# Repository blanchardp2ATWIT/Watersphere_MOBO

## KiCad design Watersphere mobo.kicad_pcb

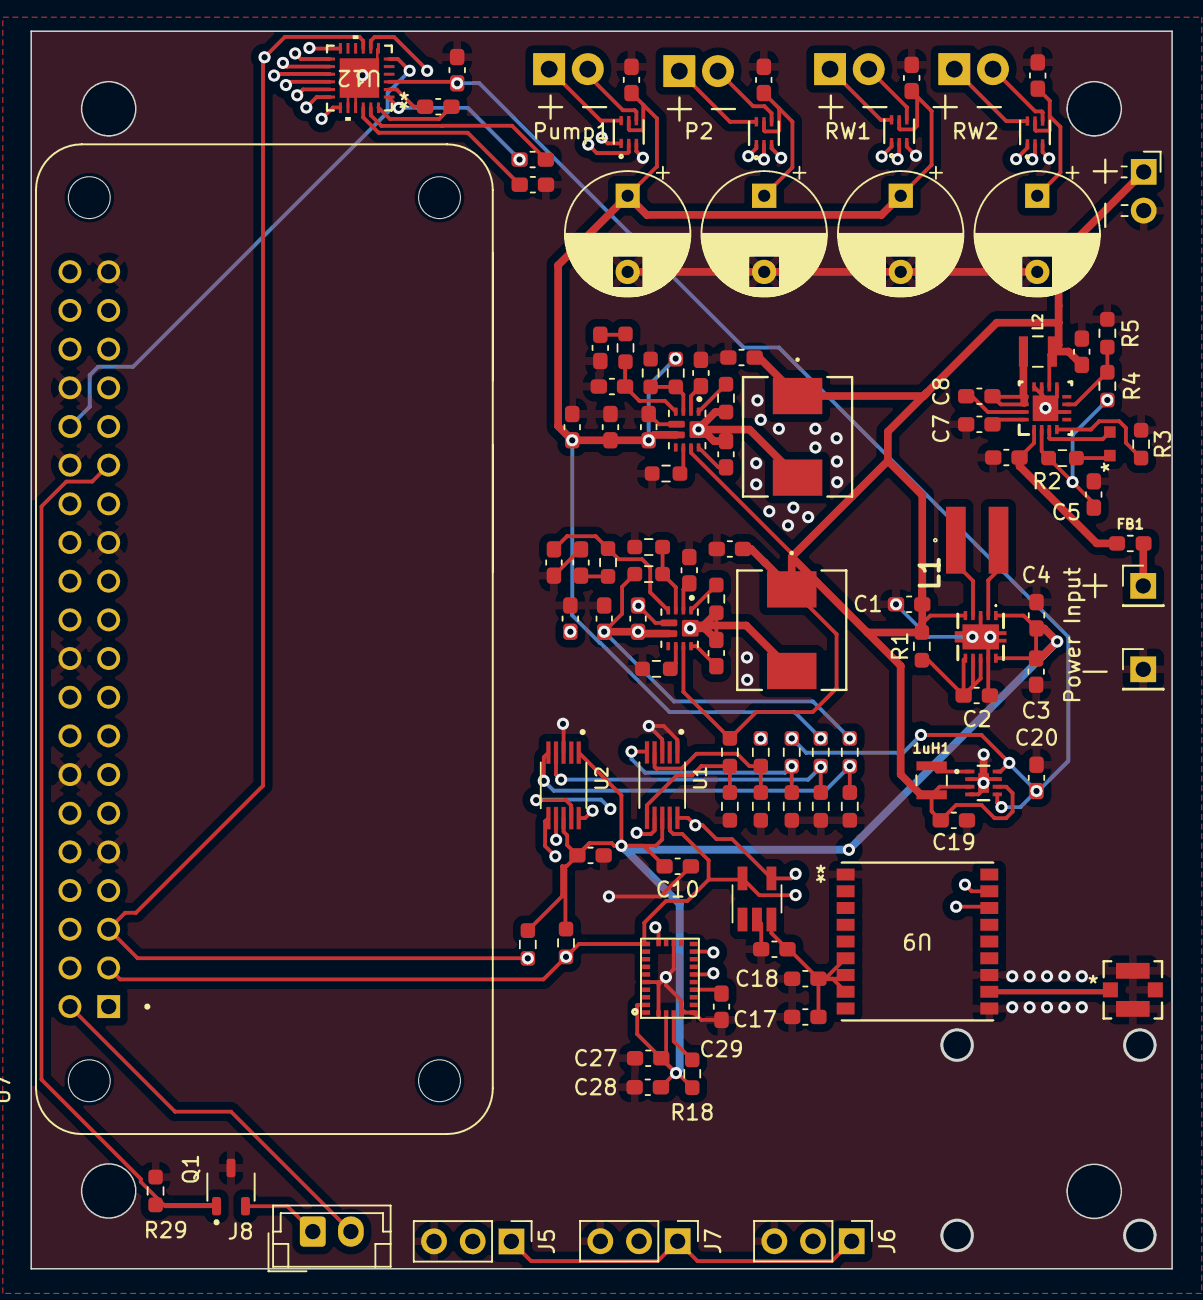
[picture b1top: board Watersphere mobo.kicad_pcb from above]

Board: 4 copper layers, 74.9 x 81.3 mm, 112 parts (0 on the bottom side), 73 nets.

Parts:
1uH1: VLS252012HBX-1R0M-1; IND_VLS252012HBX-1R0M-1
100uF1, 100uF2, 100uF3, 100uF4: C_Polarized; CP_Radial_D8.0mm_P5.00mm
C1, C3, C4, C7, C9, C17: 10 uF; C_0603_1608Metric_Pad1.08x0.95mm_HandSolder
C2: 100 nF; C_0603_1608Metric_Pad1.08x0.95mm_HandSolder
C5, C6: 2.2 uF; C_0603_1608Metric_Pad1.08x0.95mm_HandSolder
C8: 47 nF; C_0603_1608Metric_Pad1.08x0.95mm_HandSolder
C10, C11, C16, C25, C26: 1 uF; C_0603_1608Metric_Pad1.08x0.95mm_HandSolder
C12, C13, C21, C22, C27, C28, C29: .1 uF; C_0603_1608Metric_Pad1.08x0.95mm_HandSolder
C14, C30, C31, C32, C38, C39, C41, C42: 22uF; C_0603_1608Metric_Pad1.08x0.95mm_HandSolder
C15, C18, C40: 100nF; C_0603_1608Metric_Pad1.08x0.95mm_HandSolder
C19: 4.7 uF; C_0603_1608Metric_Pad1.08x0.95mm_HandSolder
C20: 22 uF; C_0603_1608Metric_Pad1.08x0.95mm_HandSolder
C23: .47 uf; C_0603_1608Metric_Pad1.08x0.95mm_HandSolder
C24: .47 uF; C_0603_1608Metric_Pad1.08x0.95mm_HandSolder
C33, C43: 2.2uF; C_0603_1608Metric_Pad1.08x0.95mm_HandSolder
C34, C37: 4.7nf; C_0603_1608Metric_Pad1.08x0.95mm_HandSolder
C35, C36: optional; C_0603_1608Metric_Pad1.08x0.95mm_HandSolder
D1: LTST-C190KRKT; LED_150060GS75000_WRE-M
IC1: BQ25303JRTER; RTE0016C_NV
J2, J3: Conn_01x01_Pin; PinHeader_1x01_P2.54mm_Vertical
J4: 691213710002; PinSocket_1x02_P2.54mm_Horizontal
J5, J6, J7: Pressure Sensor I/O; PinHeader_1x03_P2.54mm_Vertical
J8: JST_02; JST_EH_B2B-EH-A_1x02_P2.50mm_Vertical
L1: 2.2 uH; VLS4012
L2: 1 uH; IND_VLS252012HBX-1R0M-1
L3, L4: 1.8uH; IND_7030-WE-LHMI_WRE-L
MC1: SOT-23-5_HandSoldering
MI0603M121R-1: 100 ohm; L_0603_1608Metric_Pad1.05x0.95mm_HandSolder
Pump1, Pump2: Screw_Terminal_01x02; TerminalBlock_TE_282834-2_1x02_P2.54mm_Horizontal
Pump1Controller1, Pump2Controller1: DRV8212DRLR; SOT6_DRV8212_TEX-L
Q1: AO3400A; SOT95P280X125-3N
R1: 100; R_0603_1608Metric_Pad0.98x0.95mm_HandSolder
R2: 1k; R_0603_1608Metric_Pad0.98x0.95mm_HandSolder
R3: 23.2k; R_0603_1608Metric_Pad0.98x0.95mm_HandSolder
R4, R5, R6, R7, R8, R9, R10, R11, R12, R13, R14, R15, R18, R29: 10k; R_0603_1608Metric_Pad0.98x0.95mm_HandSolder
R16, R17: 3.3k; R_0603_1608Metric_Pad0.98x0.95mm_HandSolder
R19, R28: 301k; R_0603_1608Metric_Pad0.98x0.95mm_HandSolder
R20, R25: 681k; R_0603_1608Metric_Pad0.98x0.95mm_HandSolder
R21, R27: 107k; R_0603_1608Metric_Pad0.98x0.95mm_HandSolder
R22, R26: 127k; R_0603_1608Metric_Pad0.98x0.95mm_HandSolder
R23, R24: 17.4k; R_0603_1608Metric_Pad0.98x0.95mm_HandSolder
ReactionWheel1, ReactionWheel2: Screw_Terminal_01x02; TerminalBlock_TE_282834-2_1x02_P2.54mm_Horizontal
ReactionWheel1Controller1, ReactionWheel2Controller1: DRV8212DRLR; SOT6_DRV8212_TEX-L
U1, U2: ADS1115IDGSR; SOP50P490X110-10N
U3: TPS63001DRCR; TPS63002DRCT
U4: BNO055; LGA28R50P4X10_380X520X100
U5, U6: TPS61089RNRR; IC_TPS61089RNRR
U7: ADA3708; MODULE_ADA3708
U8: MIC2876-5.0YMT-TR; UDFN8_2X2_MCH-L
U9: TESEO-LIV3R; ARRAY_LIV3R_STM
U10: 734120114; 73412-0114_MOL
U12: LP55231SQE_NOPB; RTW24_TEX

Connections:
9v(1): 100uF1.1, 100uF3.1, C12.1, C21.1, C30.1, C31.1, C32.1, Pump1Controller1.5 (VM), R12.1, R20.2, ReactionWheel1Controller1.5 (VM), U5.6 (VOUT)
9v(1)_meas: R12.2, R13.1, U2.4 (AIN0)
9v(2): 100uF2.1, 100uF4.1, C13.1, C22.1, C39.1, C41.1, C42.1, Pump2Controller1.5 (VM), R14.1, R25.2, ReactionWheel2Controller1.5 (VM), U6.6 (VOUT)
9v(2)_meas: R14.2, R15.1, U2.5 (AIN1)
+3.3V: C3.1, C4.1, C10.1, C11.1, C16.2, C17.1, C18.1, C27.1, C28.1, MC1.3 (VDD), R8.1, R16.1, R17.1, R18.1, U1.8 (VDD), U2.1 (ADDR), U2.8 (VDD), U3.1 (VOUT), U3.10 (FB), U4.3 (VDD), U4.28 (VDDIO), U9.6 (VBATT), U9.7 (VCC_IO), U9.8 (VCC)
+3.3V_meas: R8.2, R9.1, U1.4 (AIN0)
+5V_meas: R10.2, R11.1, U1.5 (AIN1)
+5v: C20.1, C25.1, J5.1, J6.1, J7.1, J8.2, R10.1, U7.2 (5V_1), U8.5 (OUTS), U8.8 (OUT), U12.3 (VDD)
BAT+: 1uH1.1, C1.1, C9.1, C14.1, C19.2, C38.1, IC1.10 (BAT), J4.1, L2.2, L3.1, L4.1, R1.2, R6.1, U3.5 (VIN), U5.9 (VIN), U6.9 (VIN), U8.3 (IN), U8.6 (EN)
BAT+_meas: R6.2, R7.1, U1.6 (AIN2)
BNO_BOOTN: U4.11 (NRESET), U7.15 (GPIO22_GEN3)
BNO_Data_Ready: U4.14 (INT), U7.13 (GPIO27_GEN2)
GND: 100uF1.2, 100uF2.2, 100uF3.2, 100uF4.2, C1.2, C2.2, C3.2, C4.2, C5.2, C6.2, C7.2, C9.2, C10.2, C11.2, C12.2, C13.2, C14.2, C16.1, C17.2, C18.2, C19.1, C20.2, C21.2, C22.2, C25.2, C26.2, C27.2, C28.2, C29.2, C30.2, C31.2, C32.2, C33.2, C34.1, C35.1, C36.1, C37.1, C38.2, C39.2, C41.2, C42.2, C43.2, IC1.6 (~EN), IC1.9 (VSET), IC1.11 (GND_1), IC1.12 (GND_2), IC1.17 (EP), J3.1, J4.2, J5.3, J6.3, J7.3, MC1.2 (GND), Pump1Controller1.3 (GND), Pump2Controller1.3 (GND), Q1.3, R3.1, R5.1, R7.2, R9.2, R11.2, R13.2, R15.2, R21.2, R22.1, R26.1, R27.2, R29.2, ReactionWheel1Controller1.3 (GND), ReactionWheel2Controller1.3 (GND), U1.1 (ADDR), U1.3 (GND), U2.3 (GND), U3.3 (PGND), U3.9 (GND), U3.11 (PAD), U4.2 (GND), U4.5 (PS1), U4.6 (PS0), U4.17 (COM3), U4.25 (GNDIO), U5.5 (GND), U6.5 (GND), U7.9 (GND_1), U7.14 (GND_4), U7.20 (GND_5), U7.25 (GND_2), U7.30 (GND_6), U7.34 (GND_7), U7.39 (GND_3), U8.2 (PGND), U8.4 (AGND), U8.7 (/PG), U8.9 (AGND), U9.1 (GND), U9.10 (GND_RF), U9.12 (GND_RF), U10.2 (GROUND), U10.3 (GROUND), U10.4 (GROUND), U12.4 (GND), U12.5 (EN), U12.7 (INT), U12.10 (TRIG), U12.20 (ASELO), U12.21 (ASEL1)
I2C_Bus1_SCL: MC1.4 (SCL), R17.2, U1.10 (SCL), U2.10 (SCL), U4.19 (COM1), U7.5 (GPIO3_SCL), U9.17 (SCL), U12.9 (SCL)
I2C_Bus1_SDA: MC1.5 (SDA), R16.2, U1.9 (SDA), U2.9 (SDA), U4.20 (COM0), U7.3 (GPIO2_SDA), U9.16 (SDA), U12.8 (SDA)
Misc. Sensor 1: J6.2, U2.6 (AIN2)
Misc. Sensor 2: J7.2, U2.7 (AIN3)
unnamed: C34.2, R23.2
unnamed: C37.2, R24.2
unnamed: C8.2, IC1.15 (BTST)
unnamed: IC1.4 (ICHG), R3.2
unnamed: C7.1, IC1.16 (PMID)
unnamed: C8.1, IC1.13 (SW_1), IC1.14 (SW_2), L2.1
unnamed: IC1.7 (TS), R4.2, R5.2
unnamed: J2.1, MI0603M121R-1.1
unnamed: J8.1, Q1.2
unnamed: C2.1, R1.1, U3.6 (EN), U3.7 (PS_SYNC), U3.8 (VINA)
unnamed: L1.1, U3.4 (L1)
unnamed: L1.2, U3.2 (L2)
unnamed: C29.1, U4.9 (CAP)
unnamed: R18.2, U4.4 (NBOOT_LOAD_PIN)
unnamed: C15.1, U5.10 (BOOT)
unnamed: C35.2, R23.1, U5.4 (COMP)
unnamed: R20.1, R21.1, U5.3 (FB)
unnamed: R19.1, U5.1 (FSW)
unnamed: R22.2, U5.8 (ILIM)
unnamed: C15.2, L3.2, R19.2, U5.11 (SW)
unnamed: C33.1, U5.2 (VCC)
unnamed: C40.1, U6.10 (BOOT)
unnamed: C36.2, R24.1, U6.4 (COMP)
unnamed: R25.1, R27.1, U6.3 (FB)
unnamed: R28.1, U6.1 (FSW)
unnamed: R26.2, U6.8 (ILIM)
unnamed: C40.2, L4.2, R28.2, U6.11 (SW)
unnamed: C43.1, U6.2 (VCC)
unnamed: 1uH1.2, U8.1 (SW)
unnamed: U9.11 (RF_IN), U10.1 (SIGNAL)
unnamed: C23.1, U12.2 (C1+)
unnamed: C23.2, U12.24 (C1-)
unnamed: C24.1, U12.1 (C2+)
unnamed: C24.2, U12.23 (C2-)
unnamed: C26.1, U12.22 (VOUT)
PS_Analog_V: J5.2, U1.7 (AIN3)
PWM_1: ReactionWheel1Controller1.1 (IN1), U12.19 (D1)
PWM_2: ReactionWheel1Controller1.2 (IN2), U12.18 (D2)
PWM_3: ReactionWheel2Controller1.1 (IN1), U12.17 (D3)
PWM_4: ReactionWheel2Controller1.2 (IN2), U12.16 (D4)
PWM_5: Pump1Controller1.1 (IN1), U12.12 (D8)
PWM_6: Pump1Controller1.2 (IN2), U12.13 (D7)
PWM_7: Pump2Controller1.1 (IN1), U12.14 (D6)
PWM_8: Pump2Controller1.2 (IN2), U12.15 (D5)
PWM_Expander_CLK: U7.32 (GPIO12), U12.6 (CLK)
Pump1+: Pump1.1, Pump1Controller1.6 (OUT1)
Pump1-: Pump1.2, Pump1Controller1.4 (OUT2)
Pump2+: Pump2.1, Pump2Controller1.6 (OUT1)
Pump2-: Pump2.2, Pump2Controller1.4 (OUT2)
REGN: C5.1, IC1.2 (REGN), R2.1, R4.1
ReactionWheel1+: ReactionWheel1.1, ReactionWheel1Controller1.6 (OUT1)
ReactionWheel1-: ReactionWheel1.2, ReactionWheel1Controller1.4 (OUT2)
ReactionWheel2+: ReactionWheel2.1, ReactionWheel2Controller1.6 (OUT1)
ReactionWheel2-: ReactionWheel2.2, ReactionWheel2Controller1.4 (OUT2)
Solenoid_Driver: Q1.1, R29.1, U7.29 (GPIO5)
VIN: C6.1, IC1.1 (VBUS), MI0603M121R-1.2

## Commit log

2024-05-07 Init
2024-05-07 Updated some tings nothing important
2024-05-16 Lotta stuff added
2024-05-21 Motor Controller tings
2024-06-04 routing
2024-06-18 Routing begin
2024-06-25 Deesign Rules
2024-06-25 Done wit Drc Ignore PWM Expander for now
2024-06-25 gps started
2024-06-27 Tedi Check dis over pls.
2024-06-27 Updated a couple traces
2024-07-02 Final Rev to Send to Board house.
